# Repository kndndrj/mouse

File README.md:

# Mouse

Computer mouse from scratch.

This repository serves as an appendix to my master thesis.

New features and bugfixes won't be added to this repository.
I plan on separating different parts of the repository into
a bigger project sometime in the future. If you come across
this repository before I do that, feel free to open an issue here.

## Overview

This repository contains blueprints for building a computer mouse.

### PCB

The pcb is made using Kicad with components from LCSC, to support assembly service from JLCPCB.

[more](pcb/)

### Housing

Housing (or case) is designed in Fusion360 and is meant to be 3D printed using SLS (also available on JLCPCB).

[more](housing/)

### Firmware

First iteration of the firmware was written in C using libopencm3 library.
Due to a lack of higher level ergonomics and support for board specific abstractions,
it was later re-written in Rust.

The new version of firmware is split into 2 parts:

- **Drivers for various components** (e.g. sensor, encoder...) are exposed as a library using embedded-hal
  traits as abstraction. It is intended to be portable across different hardware and possibly used in
  other mouse-related projects.
- **Board specific implementation** is essentially just glue-code between hardware specifics and modules
  from the forementioned library.

[more - C](firmware-c/)

[more - Rust](firmware-rust/)

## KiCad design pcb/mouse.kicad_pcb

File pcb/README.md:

# Mouse PCB
Repository for the mouse circuit board schematics.

Some of the features are:
- PMW3360DM sensor
- STM32F042K6T6 MCU
- Hardware debouncing
- Expansion pins for future upgrades
- USB-C

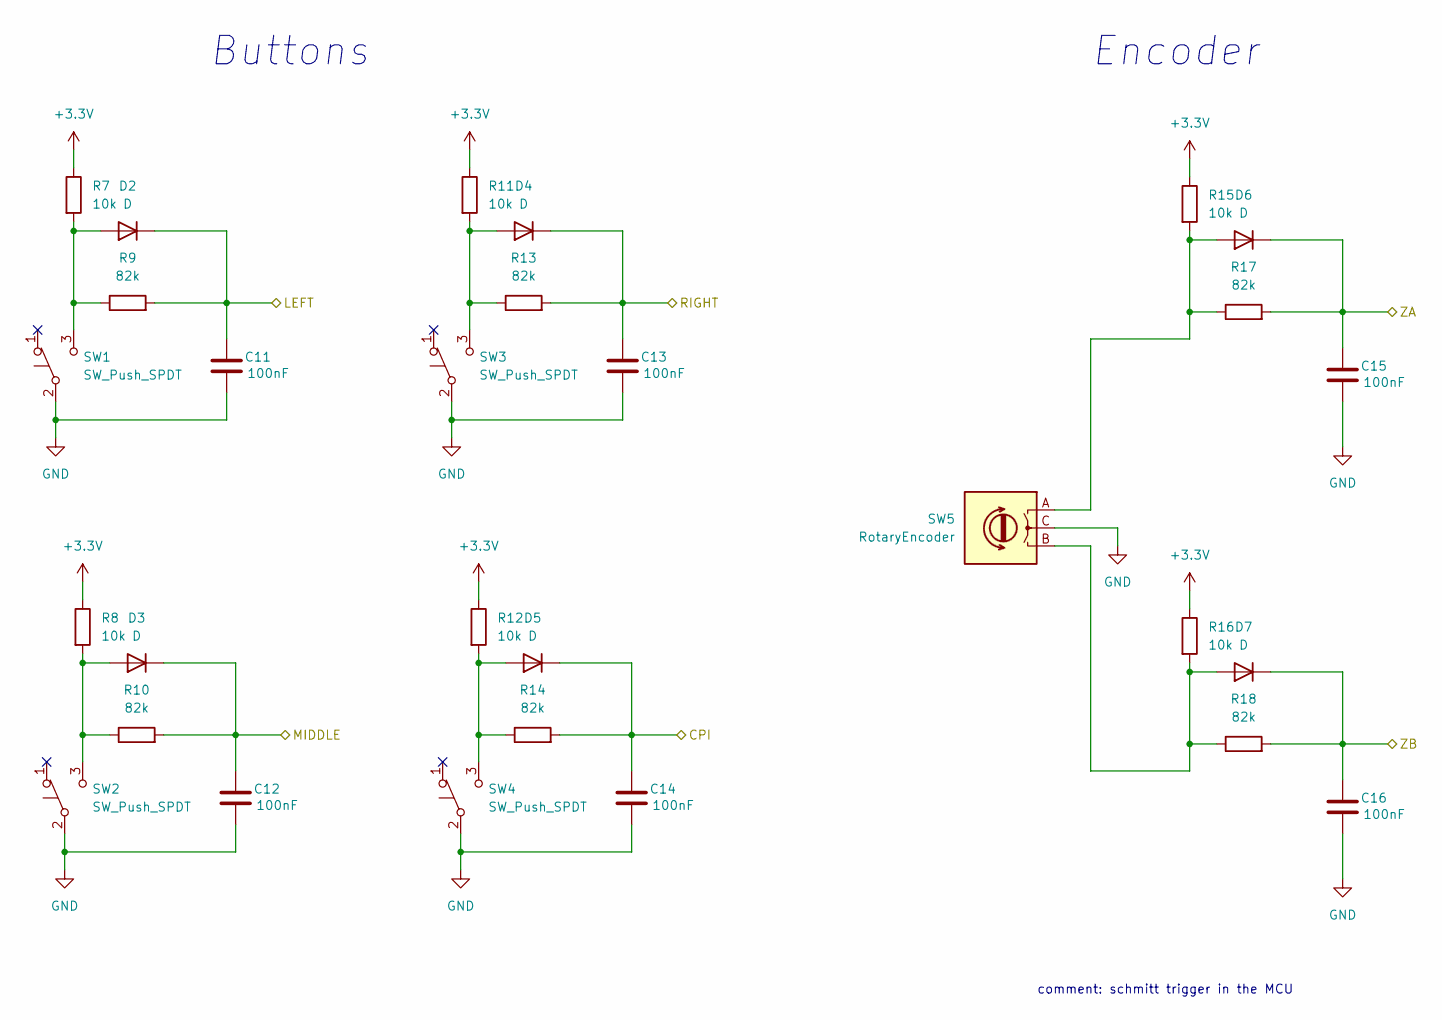
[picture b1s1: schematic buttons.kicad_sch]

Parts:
C11, C12, C13, C14, C15, C16: 100nF; C_0603_1608Metric; LCSC C14663
D2, D3, D4, D5, D6, D7: D; D_SOD-123F; LCSC C64898
R7, R8, R11, R12, R15, R16: 10k; R_0603_1608Metric; LCSC C25804
R9, R10, R13, R14, R17, R18: 82k; R_0603_1608Metric; LCSC C23254
SW1, SW2, SW3, SW4: SW_Push_SPDT; mouse_switch
SW5: RotaryEncoder; mouse_encoder

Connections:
/buttons/CPI: C14.1, D5.1 (K), R14.2; also elsewhere on the board
/buttons/LEFT: C11.1, D2.1 (K), R9.2; also elsewhere on the board
/buttons/MIDDLE: C12.1, D3.1 (K), R10.2; also elsewhere on the board
/buttons/RIGHT: C13.1, D4.1 (K), R13.2; also elsewhere on the board
/buttons/ZA: C15.1, D6.1 (K), R17.2; also elsewhere on the board
/buttons/ZB: C16.1, D7.1 (K), R18.2; also elsewhere on the board
GND: C11.2, C12.2, C13.2, C14.2, C15.2, C16.2, SW1.2 (B), SW2.2 (B), SW3.2 (B), SW4.2 (B), SW5.C; also elsewhere on the board
unnamed: D2.2 (A), R7.2, R9.1, SW1.3 (C)
unnamed: D3.2 (A), R8.2, R10.1, SW2.3 (C)
unnamed: D4.2 (A), R11.2, R13.1, SW3.3 (C)
unnamed: D5.2 (A), R12.2, R14.1, SW4.3 (C)
unnamed: D6.2 (A), R15.2, R17.1, SW5.A
unnamed: D7.2 (A), R16.2, R18.1, SW5.B

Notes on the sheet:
Encoder
Buttons
comment: schmitt trigger in the MCU

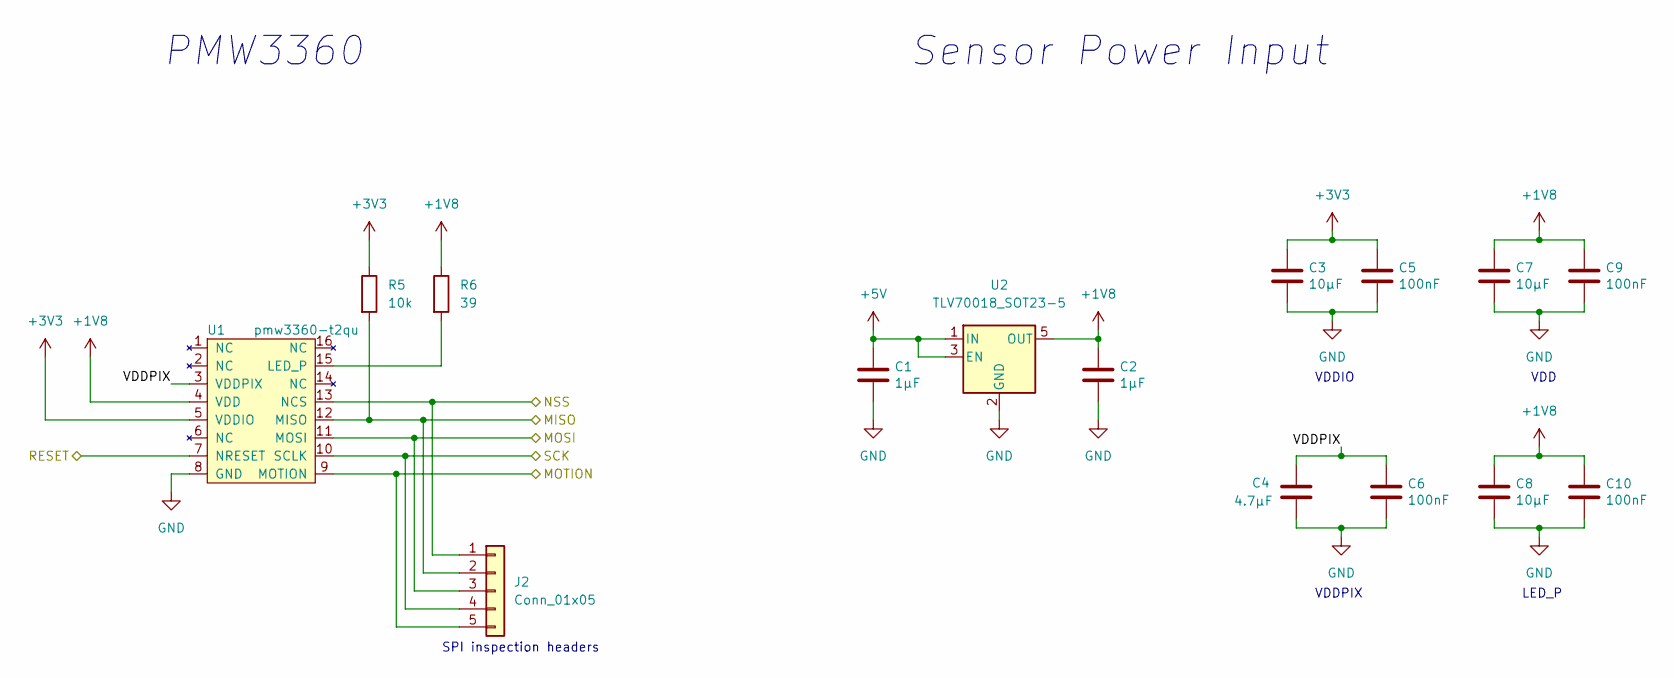
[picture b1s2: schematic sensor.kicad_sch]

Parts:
C1, C2: 1μF; C_0603_1608Metric; LCSC C15849
C3, C7, C8: 10μF; C_0603_1608Metric; LCSC C19702
C4: 4.7μF; C_0603_1608Metric; LCSC C19666
C5, C6, C9, C10: 100nF; C_0603_1608Metric; LCSC C14663
J2: Conn_01x05; PinHeader_1x05_P2.54mm_Vertical
R5: 10k; R_0603_1608Metric; LCSC C25804
R6: 39; R_0603_1608Metric; LCSC C227890
U1: pmw3360-t2qu
U2: TLV70018_SOT23-5; SOT-23-5; LCSC C79924

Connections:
+1V8: C2.1, C7.1, C8.1, C9.1, C10.1, R6.1, U1.4 (VDD), U2.5 (OUT)
+5V: C1.1, U2.1 (IN), U2.3 (EN); also elsewhere on the board
/mcu/SENSOR_MISO: J2.2, R5.2, U1.12 (MISO); also elsewhere on the board
/mcu/SENSOR_MOSI: J2.3, U1.11 (MOSI); also elsewhere on the board
/mcu/SENSOR_MOTION: J2.5, U1.9 (MOTION); also elsewhere on the board
/mcu/SENSOR_NSS: J2.1, U1.13 (NCS); also elsewhere on the board
/mcu/SENSOR_RESET: U1.7 (NRESET); also elsewhere on the board
/mcu/SENSOR_SCK: J2.4, U1.10 (SCLK); also elsewhere on the board
/sensor/VDDPIX: C4.1, C6.1, U1.3 (VDDPIX)
GND: C1.2, C2.2, C3.2, C4.2, C5.2, C6.2, C7.2, C8.2, C9.2, C10.2, U1.8 (GND), U2.2 (GND); also elsewhere on the board
unnamed: R6.2, U1.15 (LED_P)

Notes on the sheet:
VDDIO
VDD
SPI inspection headers
Sensor Power Input
LED_P
VDDPIX
PMW3360

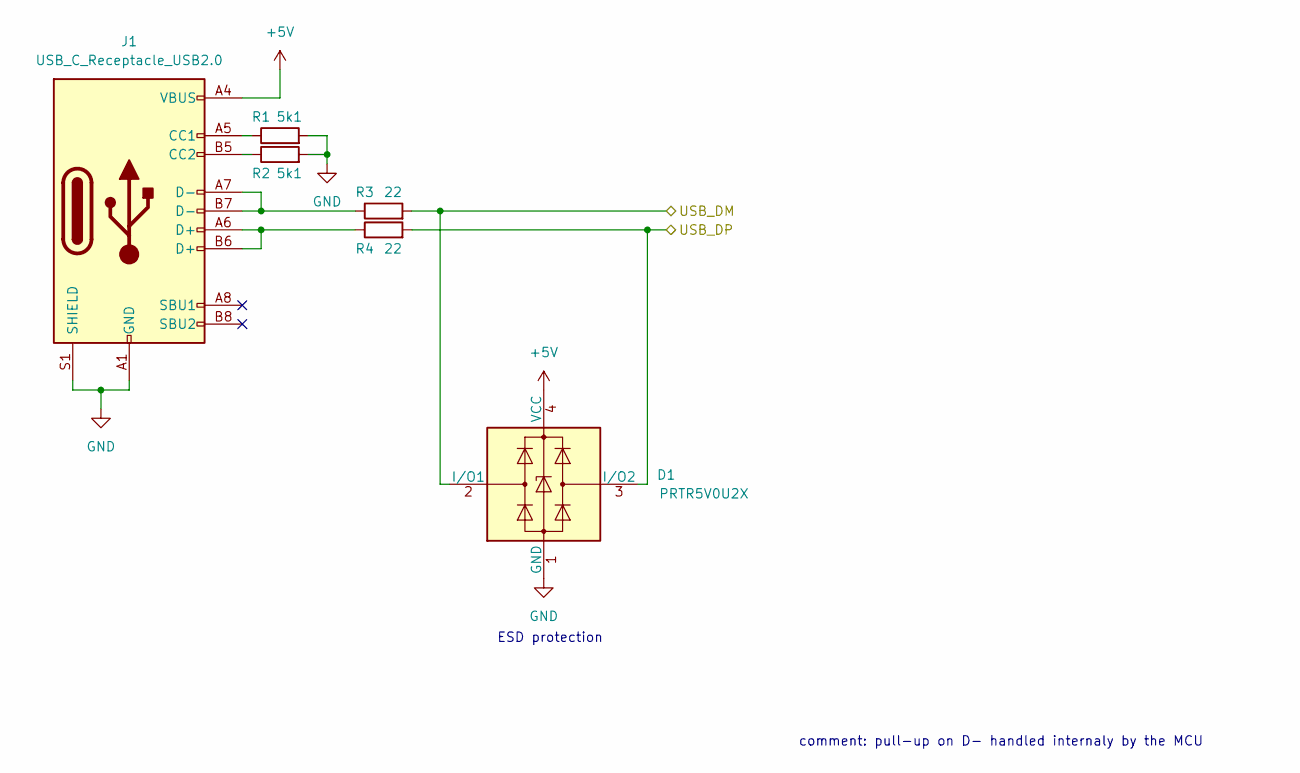
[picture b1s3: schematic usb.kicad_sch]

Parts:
D1: PRTR5V0U2X; SOT-143; LCSC C2827688
J1: USB_C_Receptacle_USB2.0; USB_C_Receptacle_XKB_U262-16XN-4BVC11; LCSC C319148
R1, R2: 5k1; R_0603_1608Metric; LCSC C23186
R3, R4: 22; R_0603_1608Metric; LCSC C107701

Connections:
+5V: D1.4 (VCC), J1.A4 (VBUS), J1.A9 (VBUS), J1.B4 (VBUS), J1.B9 (VBUS); also elsewhere on the board
/mcu/USB_DM: D1.2 (I/O1), R3.2; also elsewhere on the board
/mcu/USB_DP: D1.3 (I/O2), R4.2; also elsewhere on the board
GND: D1.1 (GND), J1.A1 (GND), J1.A12 (GND), J1.B1 (GND), J1.B12 (GND), J1.S1 (SHIELD), R1.2, R2.2; also elsewhere on the board
unnamed: J1.A5 (CC1), R1.1
unnamed: J1.A6 (D+), J1.B6 (D+), R4.1
unnamed: J1.A7 (D-), J1.B7 (D-), R3.1
unnamed: J1.B5 (CC2), R2.1

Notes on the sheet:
ESD protection
comment: pull-up on D- handled internaly by the MCU

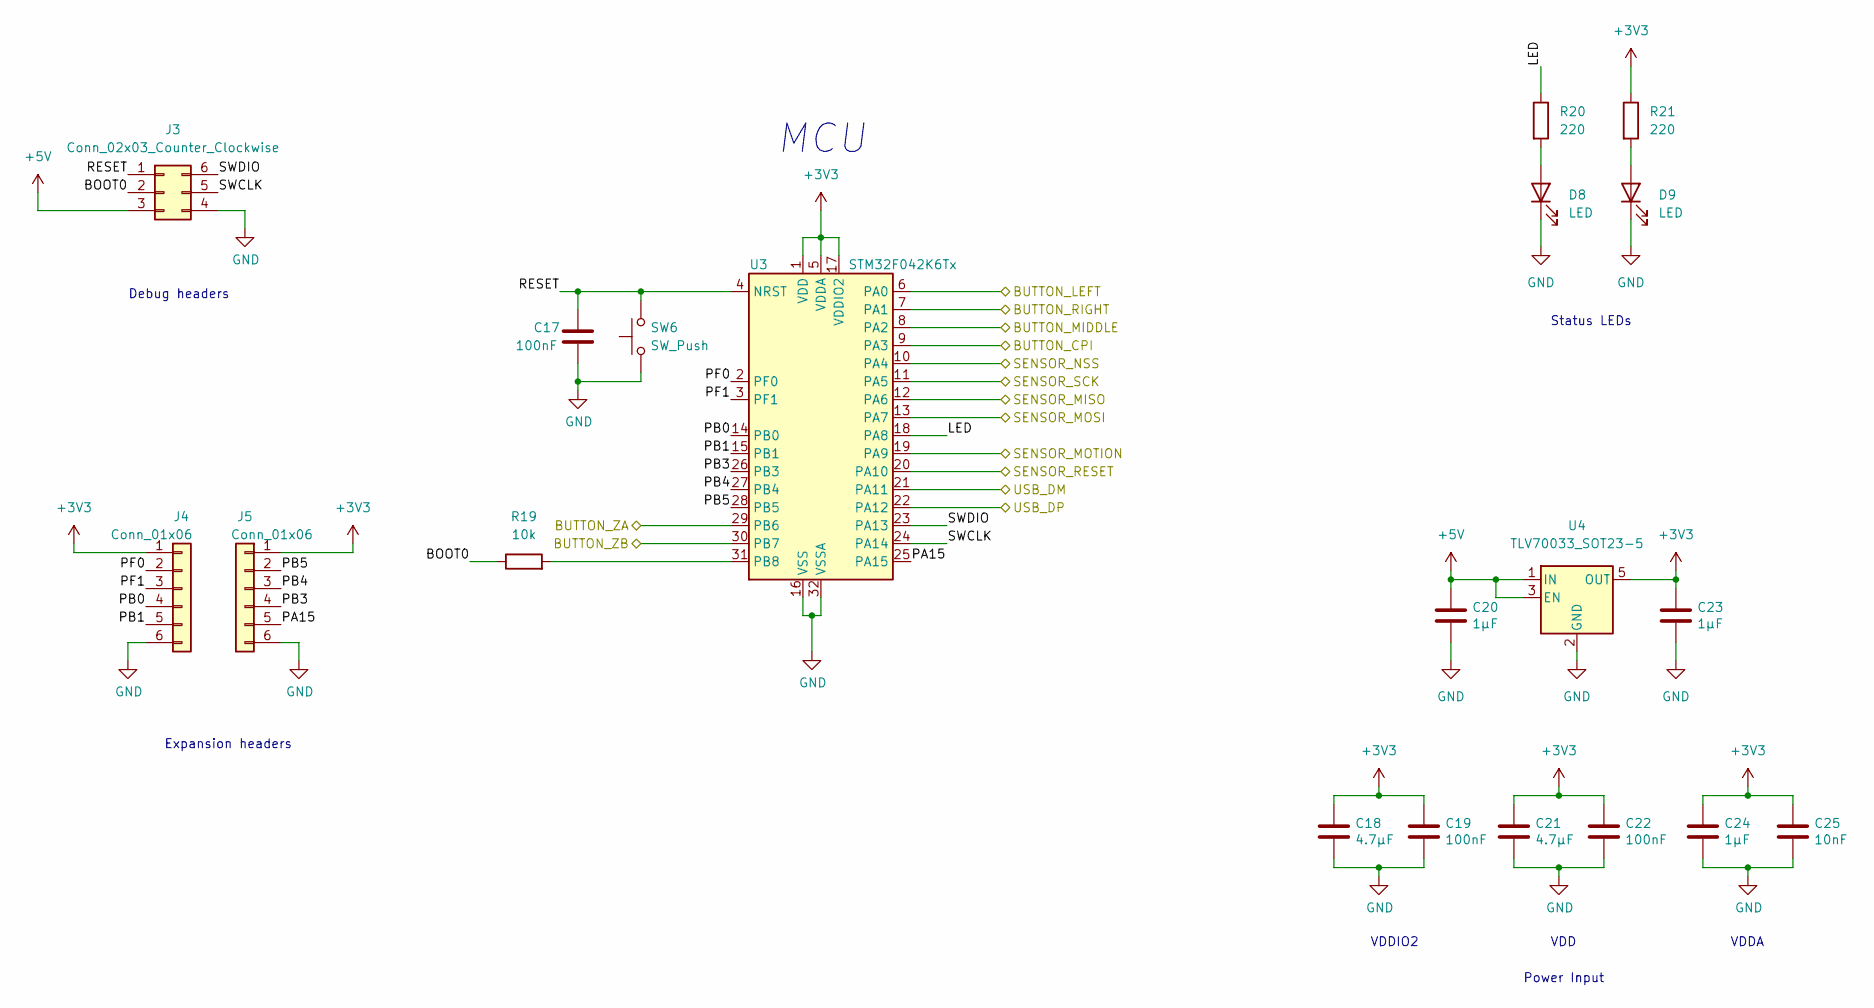
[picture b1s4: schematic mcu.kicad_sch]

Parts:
C17, C19, C22: 100nF; C_0603_1608Metric; LCSC C14663
C18, C21: 4.7μF; C_0603_1608Metric; LCSC C19666
C20, C23, C24: 1μF; C_0603_1608Metric; LCSC C15849
C25: 10nF; C_0603_1608Metric; LCSC C57112
D8, D9: LED; LED_0603_1608Metric; LCSC C72038
J3: Conn_02x03_Counter_Clockwise; PinHeader_2x03_P2.54mm_Vertical
J4, J5: Conn_01x06; PinSocket_1x06_P2.54mm_Vertical
R19: 10k; R_0603_1608Metric; LCSC C25804
R20, R21: 220; R_0603_1608Metric; LCSC C22962
SW6: SW_Push; SW_PUSH_6mm
U3: STM32F042K6Tx; LQFP-32_7x7mm_P0.8mm; LCSC C69216
U4: TLV70033_SOT23-5; SOT-23-5; LCSC C11337

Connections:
+5V: C20.1, J3.3, U4.1 (IN), U4.3 (EN); also elsewhere on the board
/buttons/CPI: U3.9 (PA3); also elsewhere on the board
/buttons/LEFT: U3.6 (PA0); also elsewhere on the board
/buttons/MIDDLE: U3.8 (PA2); also elsewhere on the board
/buttons/RIGHT: U3.7 (PA1); also elsewhere on the board
/buttons/ZA: U3.29 (PB6); also elsewhere on the board
/buttons/ZB: U3.30 (PB7); also elsewhere on the board
/mcu/BOOT0: J3.2, R19.1
/mcu/LED: R20.1, U3.18 (PA8)
/mcu/PA15: J5.5, U3.25 (PA15)
/mcu/PB0: J4.4, U3.14 (PB0)
/mcu/PB1: J4.5, U3.15 (PB1)
/mcu/PB3: J5.4, U3.26 (PB3)
/mcu/PB4: J5.3, U3.27 (PB4)
/mcu/PB5: J5.2, U3.28 (PB5)
/mcu/PF0: J4.2, U3.2 (PF0)
/mcu/PF1: J4.3, U3.3 (PF1)
/mcu/RESET: C17.1, J3.1, SW6.2, U3.4 (NRST)
/mcu/SENSOR_MISO: U3.12 (PA6); also elsewhere on the board
/mcu/SENSOR_MOSI: U3.13 (PA7); also elsewhere on the board
/mcu/SENSOR_MOTION: U3.19 (PA9); also elsewhere on the board
/mcu/SENSOR_NSS: U3.10 (PA4); also elsewhere on the board
/mcu/SENSOR_RESET: U3.20 (PA10); also elsewhere on the board
/mcu/SENSOR_SCK: U3.11 (PA5); also elsewhere on the board
/mcu/SWCLK: J3.5, U3.24 (PA14)
/mcu/SWDIO: J3.6, U3.23 (PA13)
/mcu/USB_DM: U3.21 (PA11); also elsewhere on the board
/mcu/USB_DP: U3.22 (PA12); also elsewhere on the board
GND: C17.2, C18.2, C19.2, C20.2, C21.2, C22.2, C23.2, C24.2, C25.2, D8.1 (K), D9.1 (K), J3.4, J4.6, J5.6, SW6.1, U3.16 (VSS), U3.32 (VSSA), U4.2 (GND); also elsewhere on the board
unnamed: D8.2 (A), R20.2
unnamed: D9.2 (A), R21.2
unnamed: R19.2, U3.31 (PB8)

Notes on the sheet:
Power Input
VDD
MCU
Debug headers
VDDIO2
Status LEDs
VDDA
Expansion headers

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
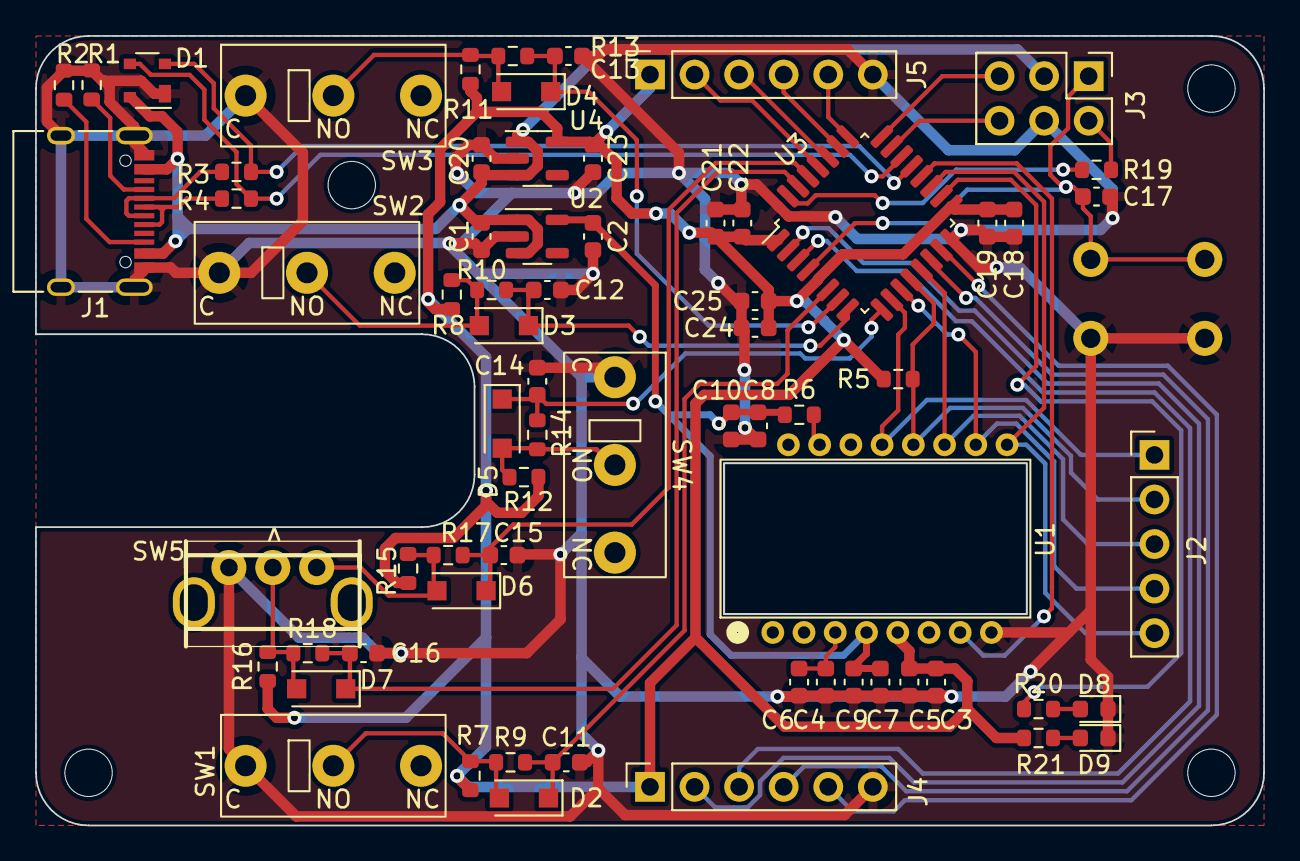
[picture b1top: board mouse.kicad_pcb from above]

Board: 2 copper layers, 70.0 x 45.0 mm, 70 parts (1 on the bottom side), 46 nets.

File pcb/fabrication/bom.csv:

Comment,Designator,Footprint,LCSC Part Number
1μF,"C1,C2,C20,C23,C24",Capacitor_SMD:C_0603_1608Metric,C15849
10nF,C25,Capacitor_SMD:C_0603_1608Metric,C57112
10μF,"C3,C7,C8",Capacitor_SMD:C_0603_1608Metric,C19702
4.7μF,"C4,C18,C21",Capacitor_SMD:C_0603_1608Metric,C19666
100nF,"C5,C6,C9,C10,C11,C12,C13,C14,C15,C16,C17,C19,C22",Capacitor_SMD:C_0603_1608Metric,C14663
PRTR5V0U2X,D1,Package_TO_SOT_SMD:SOT-143,C2827688
D,"D2,D3,D4,D5,D6,D7",Diode_SMD:D_SOD-123F,C64898
LED,"D8,D9",LED_SMD:LED_0603_1608Metric,C72038
USB_C_Receptacle_USB2.0,J1,Connector_USB:USB_C_Receptacle_XKB_U262-16XN-4BVC11,C319148
5k1,"R1,R2",Resistor_SMD:R_0603_1608Metric,C23186
220,"R20,R21",Resistor_SMD:R_0603_1608Metric,C22962
22,"R3,R4",Resistor_SMD:R_0603_1608Metric,C107701
10k,"R5,R7,R8,R11,R12,R15,R16,R19",Resistor_SMD:R_0603_1608Metric,C25804
39,R6,Resistor_SMD:R_0603_1608Metric,C227890
82k,"R9,R10,R13,R14,R17,R18",Resistor_SMD:R_0603_1608Metric,C23254
TLV70018_SOT23-5,U2,Package_TO_SOT_SMD:SOT-23-5,C79924
STM32F042K6Tx,U3,Package_QFP:LQFP-32_7x7mm_P0.8mm,C69216
TLV70033_SOT23-5,U4,Package_TO_SOT_SMD:SOT-23-5,C11337

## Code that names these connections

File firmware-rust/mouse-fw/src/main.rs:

#![no_std]
#![no_main]

use panic_halt as _;

use packed_struct::prelude::*;

use stm32f0xx_hal::spi::{Mode, Phase, Polarity, Spi};
use stm32f0xx_hal::{delay::Delay, pac, prelude::*};

use usbd_human_interface_device::device::mouse::WheelMouseReport;

#[cfg(not(feature = "disable_usb"))]
use {
    fugit::ExtU32,
    stm32f0xx_hal::usb::{Peripheral, UsbBus},
    usb_device::prelude::*,
    usbd_human_interface_device::{
        device::mouse::WHEEL_MOUSE_REPORT_DESCRIPTOR,
        prelude::*,
        {
            hid_class::{prelude::InterfaceProtocol, UsbPacketSize},
            interface::raw::RawInterfaceBuilder,
        },
    },
};

use cortex_m;
use cortex_m_rt::entry;

use mouse_libs::{
    debouncer::{self, Debouncer},
    encoder::Encoder,
    pmw3360::Pmw3360,
};

#[entry]
fn main() -> ! {
    let mut p = pac::Peripherals::take().unwrap();
    let cp = cortex_m::Peripherals::take().unwrap();

    // Clock
    let mut rcc = p
        .RCC
        .configure()
        .hsi48()
        .enable_crs(p.CRS)
        .sysclk(48.mhz())
        .pclk(24.mhz())
        .freeze(&mut p.FLASH);

    // Pin maps
    let gpioa = p.GPIOA.split(&mut rcc);
    let (
        button_left,
        button_right,
        button_middle,
        button_cpi,
        spi_cs,
        spi_sck,
        spi_miso,
        spi_mosi,
        pmw_reset,
        usb_dm,
        usb_dp,
    ) = cortex_m::interrupt::free(move |cs| {
        (
            // Button pins
            gpioa.pa0,
            gpioa.pa1,
            gpioa.pa2,
            gpioa.pa3,
            // SPI pins
            gpioa.pa4.into_push_pull_output(cs),
            gpioa.pa5.into_alternate_af0(cs),
            gpioa.pa6.into_alternate_af0(cs),
            gpioa.pa7.into_alternate_af0(cs),
            // PMW3360 reset pin
            gpioa.pa10.into_push_pull_output(cs),
            // USB pins
            gpioa.pa11,
            gpioa.pa12,
        )
    });

    let gpiob = p.GPIOB.split(&mut rcc);
    let (enc_a, enc_b) = cortex_m::interrupt::free(move |_| {
        (
            // Encoder pins
            gpiob.pb6, gpiob.pb7,
        )
    });

    // SPI
    const MODE: Mode = Mode {
        polarity: Polarity::IdleHigh,
        phase: Phase::CaptureOnSecondTransition,
    };
    let spi = Spi::spi1(
        p.SPI1,
        (spi_sck, spi_miso, spi_mosi),
        MODE,
        1.mhz(),
        &mut rcc,
    );

    // Delay
    let delay = Delay::new(cp.SYST, &rcc);

    // Sensor
    let mut pmw = Pmw3360::new(spi, spi_cs, pmw_reset, delay);
    pmw.set_cpi(1200).unwrap_or_default();

    // Encoder
    let mut enc = Encoder::new(enc_a, enc_b);

    // Debouncer for cpi pin
    let mut debouncer_cpi = Debouncer::new(8);

    // USB
    // NOTE: keep usb last before loop -> might not enumerate fast enough
    #[cfg(not(feature = "disable_usb"))]
    let usb_bus = UsbBus::new(Peripheral {
        usb: p.USB,
        pin_dm: usb_dm,
        pin_dp: usb_dp,
    });
    #[cfg(not(feature = "disable_usb"))]
    let mut mouse = UsbHidClassBuilder::new()
        .add_interface(
            RawInterfaceBuilder::new(WHEEL_MOUSE_REPORT_DESCRIPTOR)
                .boot_device(InterfaceProtocol::Mouse)
                .description("Wheel Mouse")
                .in_endpoint(UsbPacketSize::Bytes8, 1.millis())
                .unwrap()
                .without_out_endpoint()
                .build(),
        )
        .build(&usb_bus);
    // USB_SERIAL_NUMBER defined in build.rs at compile time
    #[cfg(not(feature = "disable_usb"))]
    let mut usb_dev = UsbDeviceBuilder::new(&usb_bus, UsbVidPid(0xc410, 0x0000))
        .manufacturer("kndndrj")
        .product("mouse")
        .serial_number(env!("USB_SERIAL_NUMBER"))
        .build();

    let mut report = WheelMouseReport::default();

    loop {
        #[cfg(not(feature = "disable_usb"))]
        {

            if !usb_dev.poll(&mut [&mut mouse]) {
                continue;
            }

            mouse.interface().write_report(&report.pack().unwrap()).ok();
        }

        report = WheelMouseReport::default();

        let motion_data = pmw.burst_read().unwrap_or_default();

        if motion_data.motion && motion_data.on_surface {
            if motion_data.dx > 127 {
                report.x = -127;
            } else if motion_data.dx < -127 {
                report.x = 127;
            } else {
                report.x = -motion_data.dx as i8;
            }

            if motion_data.dy > 127 {
                report.y = -127;
            } else if motion_data.dy < -127 {
                report.y = 127;
            } else {
                report.y = -motion_data.dy as i8;
            }
        }

        enc.update().ok();

        if report.vertical_wheel == 0 {
            report.vertical_wheel = enc.read().unwrap_or_default().count();
        }

        if button_left.is_low().unwrap_or_default() {
            report.buttons = report.buttons | (1 << 0);
        }
        if button_right.is_low().unwrap_or_default() {
            report.buttons = report.buttons | (1 << 1);
        }
        if button_middle.is_low().unwrap_or_default() {
            report.buttons = report.buttons | (1 << 2);
        }
        // Debouncer is meant to be used with a scheduler, but the buttons on our pcb are very well
        // hw debounced, so we use it to detect the edge
        let cpi_button_state = debouncer_cpi
            .update(button_cpi.is_high().unwrap_or_default())
            .unwrap_or_default();
        if cpi_button_state == debouncer::State::Low {
            let mut cpi = pmw.get_cpi().unwrap_or_default() + 2000;
            if cpi > 12000 {
                cpi = 0;
            }
            pmw.set_cpi(cpi).unwrap_or_default();
        }
    }
}

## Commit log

2021-12-07 Initial commit - rough example with sensor and usb
2021-12-12 added gpio setup for buttons and encoder
2021-12-29 - pmw3360 symbol - basic circuit for stm32f042
2021-12-29 formated both pmw3360 firmwares in sepereate files
2021-12-31 finished rough outline of the pcb, added gitignore
2021-12-31 updated to new kicad file extensions
2022-01-29 - added power input LDOs - broken out schematics to multiple sheets
2022-01-29 added pmw3360 footprint and linked it to the symbol
2022-02-03 cleaned up symbols in schematics a bit
2022-03-06 - split schematic to lists - changed global ports to local - assigned footprints to majority of schematic parts
2022-03-06 Added README.md with TODOs
2022-05-29 - added debouncing to buttons - assigned some footprints - added expansion and inspection pin headers
2022-05-29 - added rotary encoder debouncing - added mouse switch and encoder footprints - changed some symbols - assigned footprints
2022-06-12 added LCSC part numbers and assigned footprints
2022-06-12 - added status leds - changed some lcsc components
2022-06-12 - cleaned up schematics - roughly arranged components on pcb - added pcb outline
2022-06-19 - added boot select resistor - regenerated netlist - adjusted pcb component placement
2022-06-19 connected all pcb elements with tracks
2022-06-19 added pcb mounting holes
2022-06-19 fixed pcb according to DRC check
2022-06-19 added rounded corners to pcb
2022-06-24 manually connected GND on pcb
2022-06-24 connected long loose ends of pcb traces, repoured copper pours
2022-06-26 updated encoder position and widened wheel gap
2022-06-26 adjusted encoder position
2022-06-26 added usb and sensor 3d models
2022-06-26 changed 3d models to wrl
2022-06-30 Updated usb connector placement on pcb
2022-07-03 added fabrication files
2022-08-21 updated todos
2022-08-24 - added README.md - renamed include to inc - code cleanup - meson run_command fix
2022-11-16 added clang config
2022-11-16 removed dfu from main.c and formatted the file
2022-11-16 converted linker and libs to cortex-m0
2022-11-18 updated pmw firmware upload
2022-11-20 - adjusted motion burst read for stm32f0 - adjusted poll interval for usb hid endpoint
2022-11-20 - restructured meson build files
2022-11-28 - added formatting rules - restructured project: - hal - hw access per architecture - drivers - interaction with chips, buttons etc.
2022-11-28 updated libopencm3 path
2022-11-28 - added gpio hal - specified pins as combination of port and pin macro
2022-11-28 spi pins as macro structs
2022-11-28 moved f0 include to stm32 common
2022-11-28 added gpio toggle and cleaned up some init code
2022-11-28 - added button driver - added software encoder driver
2022-11-29 send mouse wheel data over usb
2022-11-30 usb device not global anymore
2022-12-01 - added switch and encoder 3d models
2022-12-02 updated todo
2022-12-03 Initial commit with example bluepill program
2022-12-03 removed rtfm stuff
2022-12-03 stm32f0 minimal hid example
2022-12-03 use prebuilt hid class
2022-12-03 added simple pmw3360 interface with working spi
2022-12-04 - added pmw3360 firmware files - implemented pmw3360 methods - send pmw3360 data over usb
2022-12-18 added encoder draft driver (non working)
2022-12-18 resolved delay sharing conflict for pmw and encoder
2022-12-18 use embedded hal interfaces instead of custom ones
2022-12-18 added feature flag for usb (for debugging)
2022-12-18 - simplified encoder code - split encoder into read and update
2022-12-28 Initial commit with exported f360 design
2023-01-04 fixed slugish encoder bug
2023-01-05 - added a debouncer - implemented buttons - renamed encoder struct
2023-01-05 implemented setting cpi
2023-01-05 prettier implementation of converting sensor data to hid report
2023-01-05 embed git version into usb strings
2023-01-05 pulled drivers into a seperate crate
2023-01-05 increase poll rate to 1000hz, change default cpi
2023-01-05 updated readmes
2023-01-05 moved from usb-hid to usbd-human-device-interface
2023-01-05 added PWR_FLAGs to pass ERC checks
2023-01-06 added ci workflows with kibot
2023-01-06 removed previous fabrication files
2023-01-20 ci: releases only on tags
2023-01-21 rearanged usb polling, updated descriptor
2023-01-21 pmw3360: - adjusted read/write timings - don't initiate burst read on every method call
2023-01-21 pmw3360: power_up is no longer public
2023-01-21 rerun build.rs if git refs change
2023-01-21 added deprecation notice
2023-01-22 added main README.md, moved assets
2023-01-22 updated github workflow for pcb
2023-01-22 updated libopencm3 submodule
2023-01-22 updated README files and added TODOs
2023-06-04 replace embedded_time with fugit, include Cargo.lock
